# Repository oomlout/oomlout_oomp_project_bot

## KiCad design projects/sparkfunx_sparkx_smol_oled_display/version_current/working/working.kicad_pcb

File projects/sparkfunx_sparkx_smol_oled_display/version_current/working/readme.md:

# OOMP Project  
## SparkX_smol_OLED_Display  by sparkfunX  
  
oomp key: oomp_projects_flat_sparkfunx_sparkx_smol_oled_display  
(snippet of original readme)  
  
- SparkX smôl Header  

[*SparkX smôl OLED Display (SPX-18996)*](https://www.sparkfun.com/products/18996)  
  
The smôl OLED Display is a high contrast, small monochrome display with 128 x 32 pixels. Perfect for applications that don't possess a lot of space but still need to communicate to the user. The display uses the common SSD1306 driver IC fully supported by our blistering fast [SparkFun Qwiic OLED Library](https://github.com/sparkfun/SparkFun_Qwiic_OLED_Arduino_Library).  

-- Repository Contents  
  
- **/Dosuments** - Driver datasheet  
- **/Hardware** - Eagle design files  
- **LICENSE.md** contains the licence information  

-- License Information  
  
This product is _**open source**_!  
  
Please review the LICENSE.md file for license information.  
  
If you have any questions or concerns on licensing, please contact technical support on our [SparkFun forums](https://forum.sparkfun.com/viewforum.php?f=123).  
  
Distributed as-is; no warranty is given.  
  
- Your friends at SparkFun.  
  
  full source readme at [readme_src.md](readme_src.md)  
  
source repo at: [https://github.com/sparkfunX/SparkX_smol_OLED_Display](https://github.com/sparkfunX/SparkX_smol_OLED_Display)  
## Board  

## Schematic  

[schematic pdf](working_schematic.pdf)  
## Images

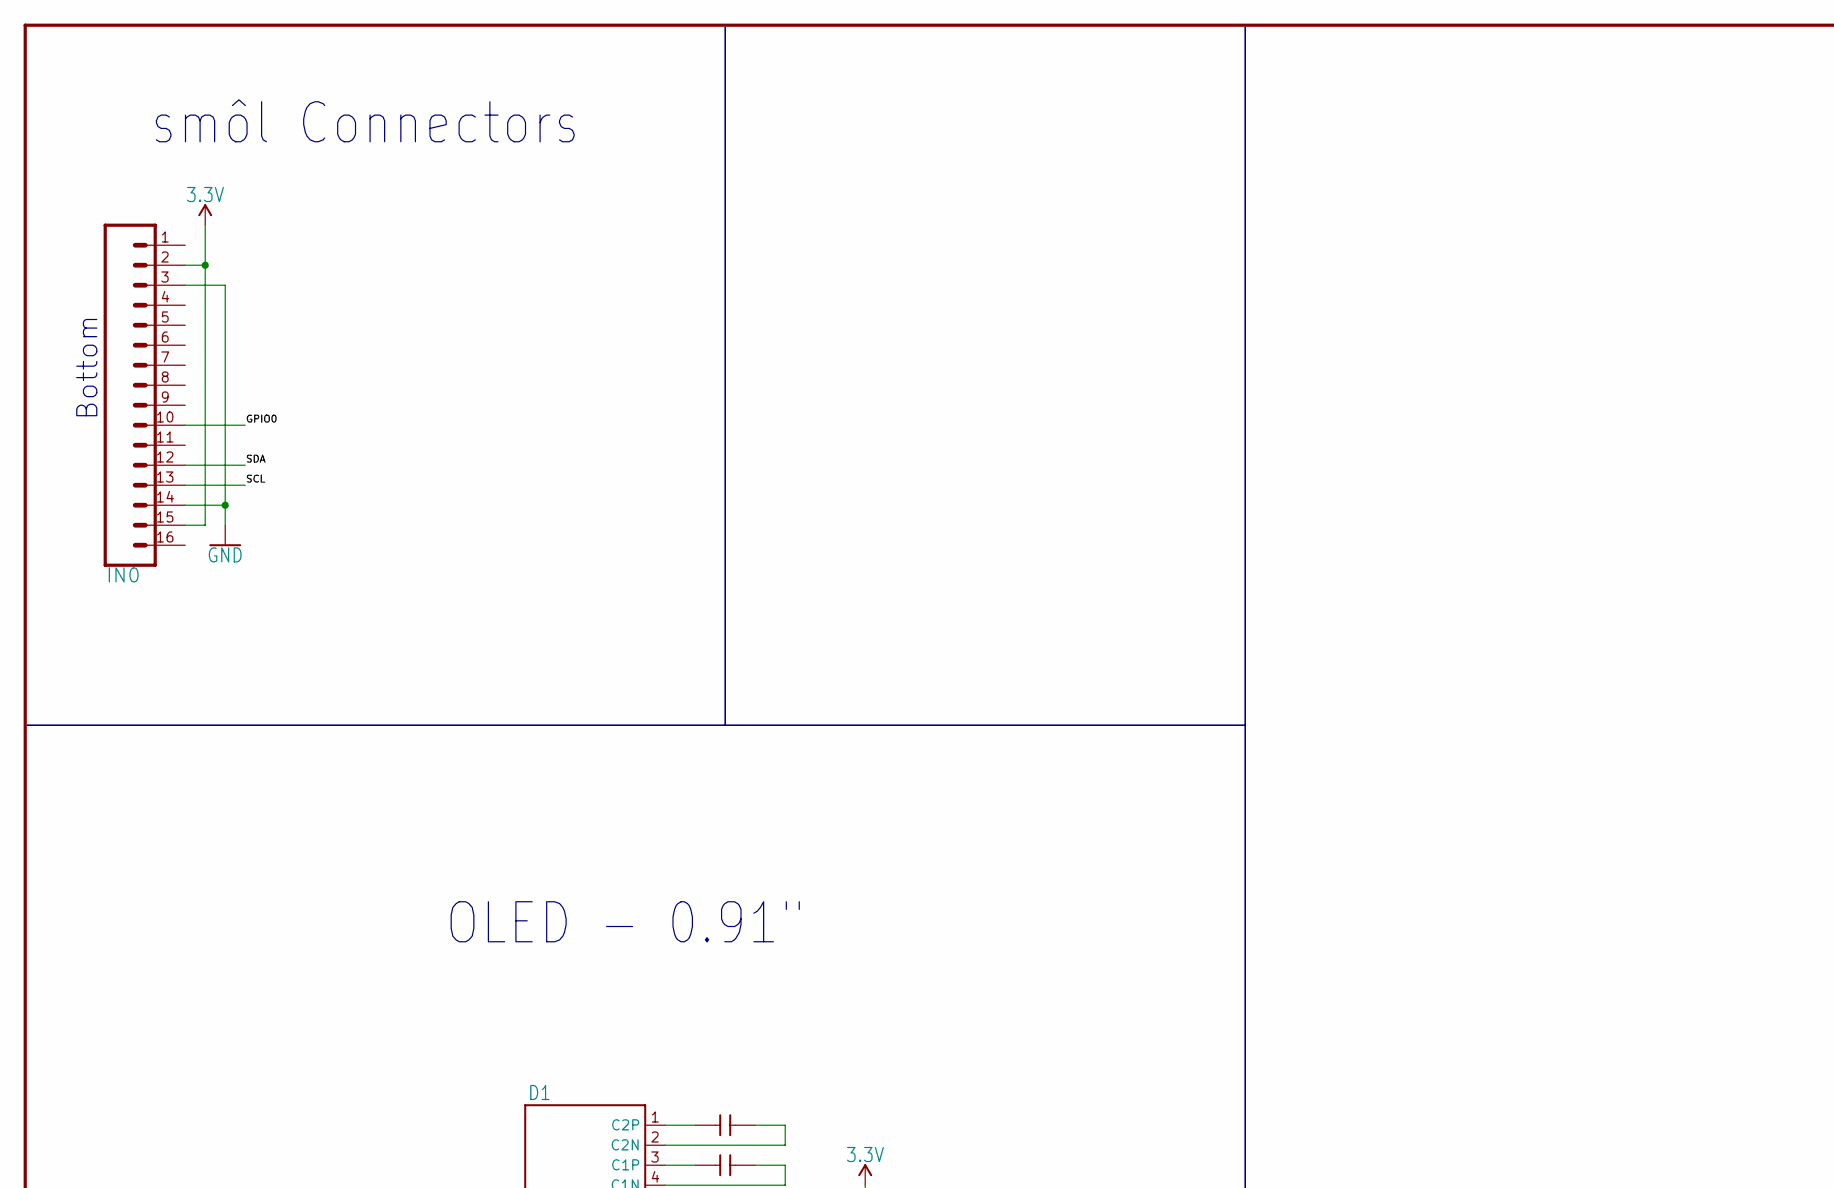
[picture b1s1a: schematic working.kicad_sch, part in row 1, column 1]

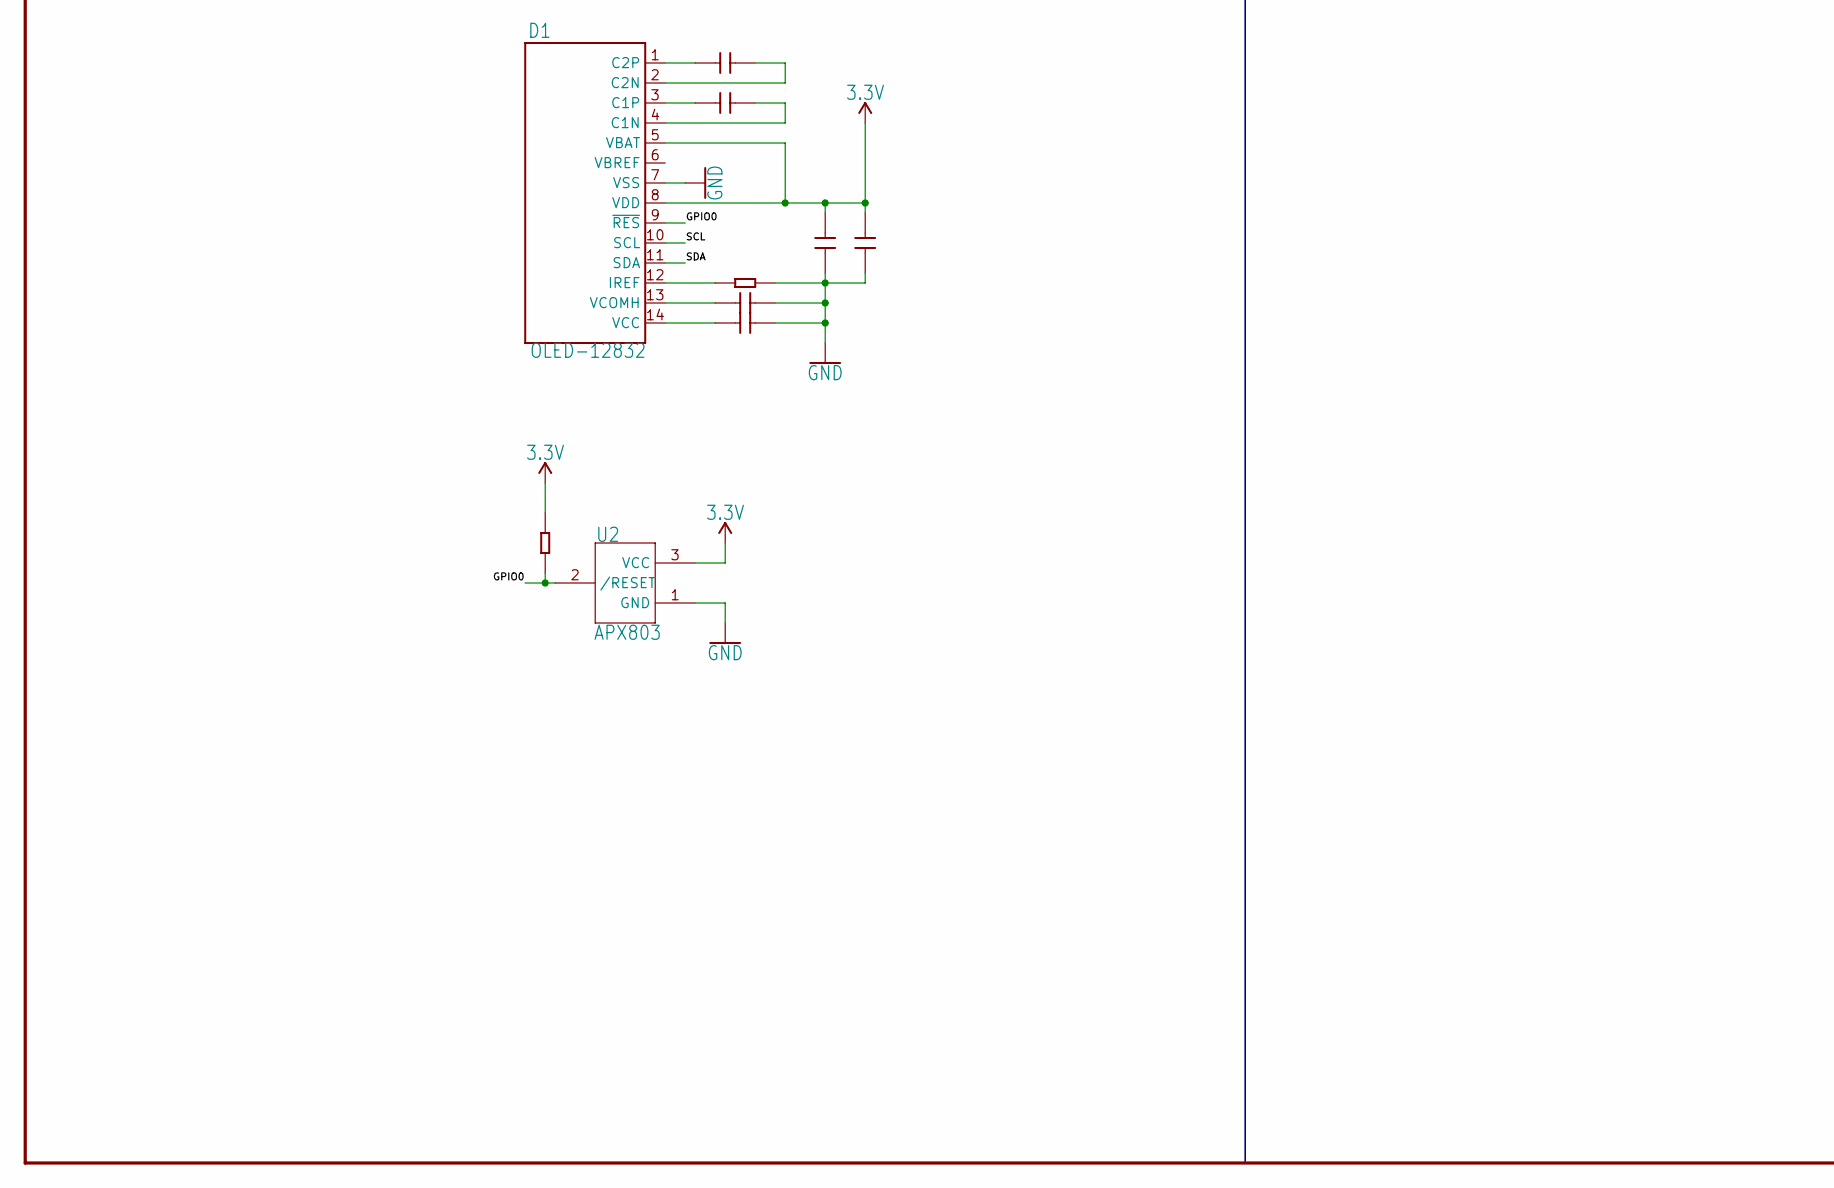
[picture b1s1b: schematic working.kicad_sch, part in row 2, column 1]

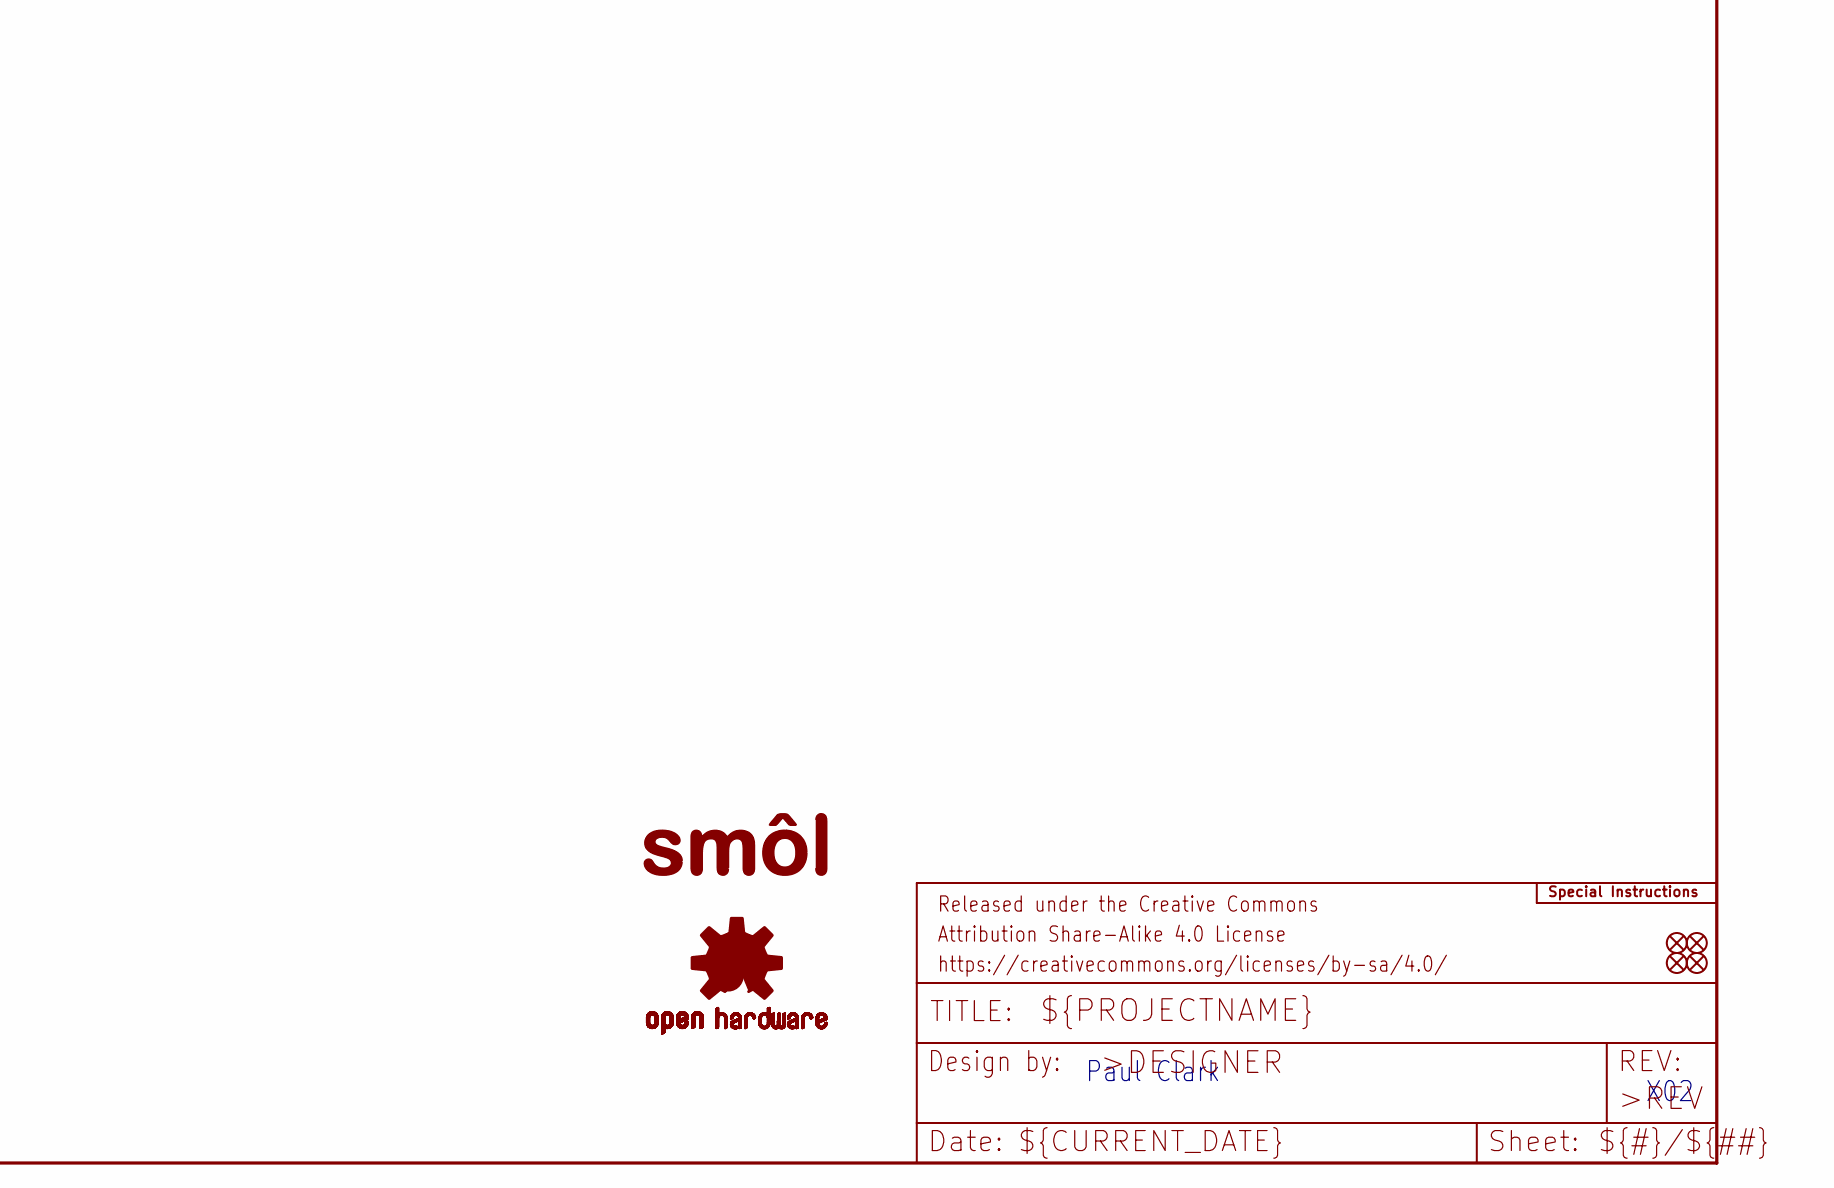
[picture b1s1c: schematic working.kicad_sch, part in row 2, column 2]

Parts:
C1, C2: 1uF ±10% 16V; 0603
C3: 4.7uF ±10% 6.3V; 0603
C4: 0.1uF ±10% 25V; 0603
C5: 2.2uF ±10% 16V; 0603
C6: 4.7uF ±10% 16V; 0603
D1: OLED-12832
FD1, FD2, FD3, FD4: FIDUCIALUFIDUCIAL; FIDUCIAL-MICRO
FRAME1: FRAME-LEDGER; CREATIVE_COMMONS
IN0: CONN_16FPC_16_0.5MM; FPC_16_0.5MM
LOGO1: SPECIAL_INSTRUCTIONS-ORDERING; ORDERING_INSTRUCTIONS
LOGO3: OSHW-LOGOMINI; OSHW-LOGO-MINI
R3: 560K 10%; 0603
R4: 10K ±5%; 0603
U2: APX803; SOT23
U$14: SMOL_LOGOSMALL; SMOL_SMALL

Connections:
3.3V: C3.1, C4.1, D1.5 (VBAT), D1.8 (VDD), IN0.2, IN0.15, R4.2, U2.3 (VCC)
GND: C3.2, C4.2, C5.2, C6.2, D1.7 (VSS), IN0.3, IN0.14, R3.1, U2.1 (GND)
GPIO0: D1.9 (~RES), IN0.10, R4.1, U2.2 (/RESET)
unnamed: C1.2, D1.1 (C2P)
unnamed: C1.1, D1.2 (C2N)
unnamed: C2.2, D1.3 (C1P)
unnamed: C2.1, D1.4 (C1N)
unnamed: C5.1, D1.13 (VCOMH)
unnamed: C6.1, D1.14 (VCC)
unnamed: D1.12 (IREF), R3.2
SCL: D1.10 (SCL), IN0.13
SDA: D1.11 (SDA), IN0.12

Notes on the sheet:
X02
Paul Clark
Bottom
OLED - 0.91"
smôl Connectors

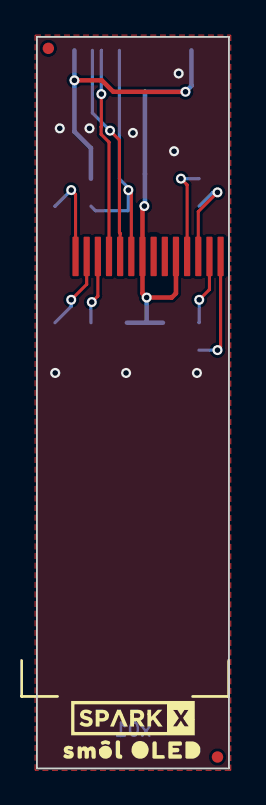
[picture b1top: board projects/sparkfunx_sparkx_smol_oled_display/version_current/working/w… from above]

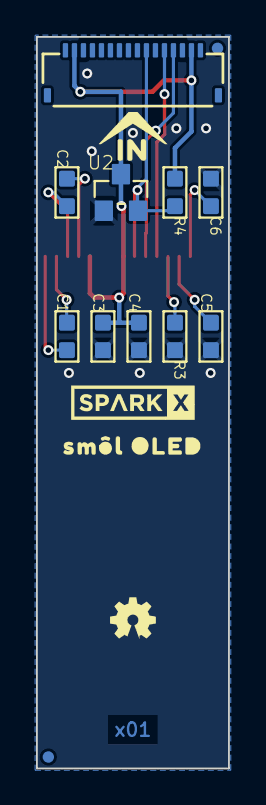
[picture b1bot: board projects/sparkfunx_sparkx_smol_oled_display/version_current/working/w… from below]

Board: 2 copper layers, 10.7 x 40.6 mm, 24 parts (17 on the bottom side), 12 nets.

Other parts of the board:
U$1, U$4: SM�L_OLED0
U$3, U$20: SPARKX-LOGO3; SPARKX-SMALL
U$12: IN0

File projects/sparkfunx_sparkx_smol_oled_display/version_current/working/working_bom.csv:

Row,Description,Part,References,Value,Footprint,Quantity Per PCB,Status,Datasheet
1,,C-0603,C4,0.1uF ±10% 25V,0603,1, ,
2,,C-0603,C1 C2,1uF ±10% 16V,0603,2, ,
3,,C-0603,C5,2.2uF ±10% 16V,0603,1, ,
4,,C-0603,C3 C6,4.7uF ±10% 6.3V,0603,2, ,
5,,OLED-12832,D1,OLED-12832,OLED-12832,1, ,
6,,FRAME-LEDGER,FRAME1,FRAME-LEDGER,CREATIVE_COMMONS,1, ,
7,,CONN_16FPC_16_0.5MM,IN0,CONN_16FPC_16_0.5MM,FPC_16_0.5MM,1, ,
8,,OSHW-LOGOMINI,LOGO3,OSHW-LOGOMINI,OSHW-LOGO-MINI,1, ,
9,,SPECIAL_INSTRUCTIONS-ORDERING,LOGO1,SPECIAL_INSTRUCTIONS-ORDERING,ORDERING_INSTRUCTIONS,1, ,
10,,R-0603,R4,10K ±5%,0603,1, ,
11,,R-0603,R3,560K 10%,0603,1, ,
12,,APX803,U2,APX803,SOT23,1, ,
13,,SMOL_LOGOSMALL,U$14,SMOL_LOGOSMALL,SMOL_SMALL,1, ,





Project info:
Schematic:,working
Variant:,default
Revision:,
Date:,2023-08-06_12-56-17
KiCad Version:,7.0.6-7.0.6~ubuntu22.04.1
Statistics:
Component Groups:,13
Component Count:,15 (0 SMD/ 0 THT)
Fitted Components:,15 (0 SMD/ 0 THT)
Number of PCBs:,1
Total Components:,15

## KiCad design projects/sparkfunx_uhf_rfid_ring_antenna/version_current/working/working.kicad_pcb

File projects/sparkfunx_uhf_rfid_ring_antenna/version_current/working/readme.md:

# UHF_RFID_Ring_Antenna by sparkfunX  
This is a harvested standardized copy of a project from github.  
The original project can be found at:  
https://github.com/sparkfunX/UHF_RFID_Ring_Antenna  
Please consult that link for additional, details, files, and license information.  
Note: It was auto harvested and if the original repo had more than one board file or anything out of the ordinary the files here are likely not representative.

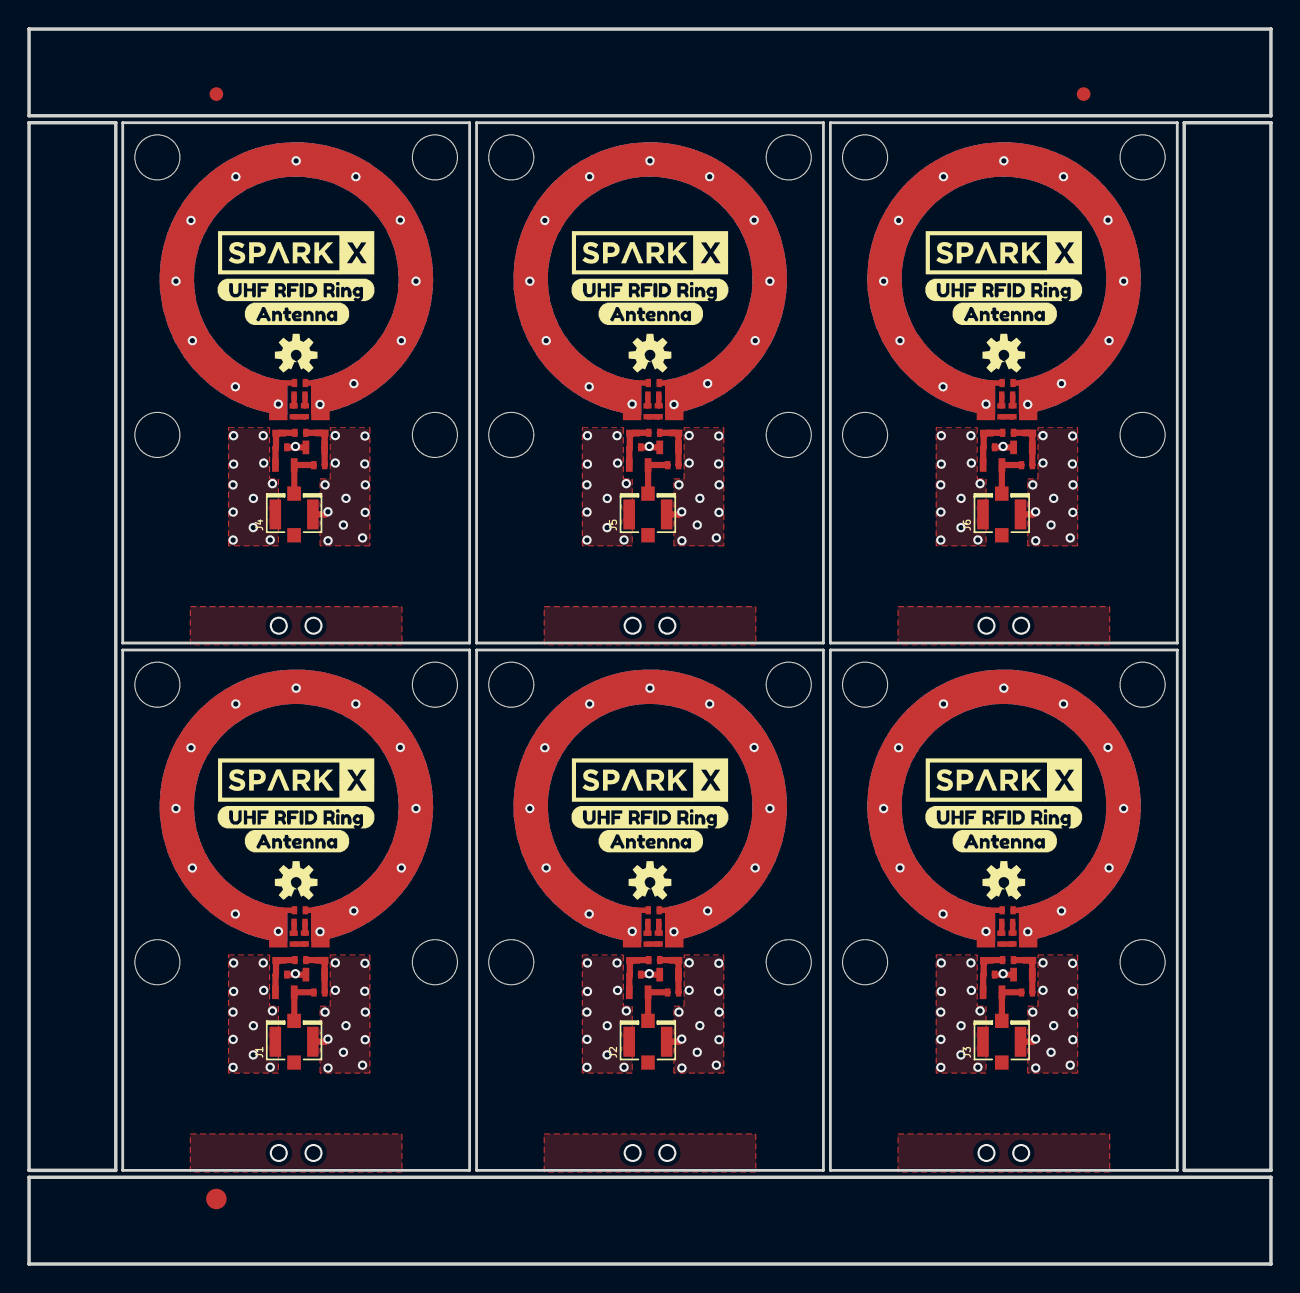
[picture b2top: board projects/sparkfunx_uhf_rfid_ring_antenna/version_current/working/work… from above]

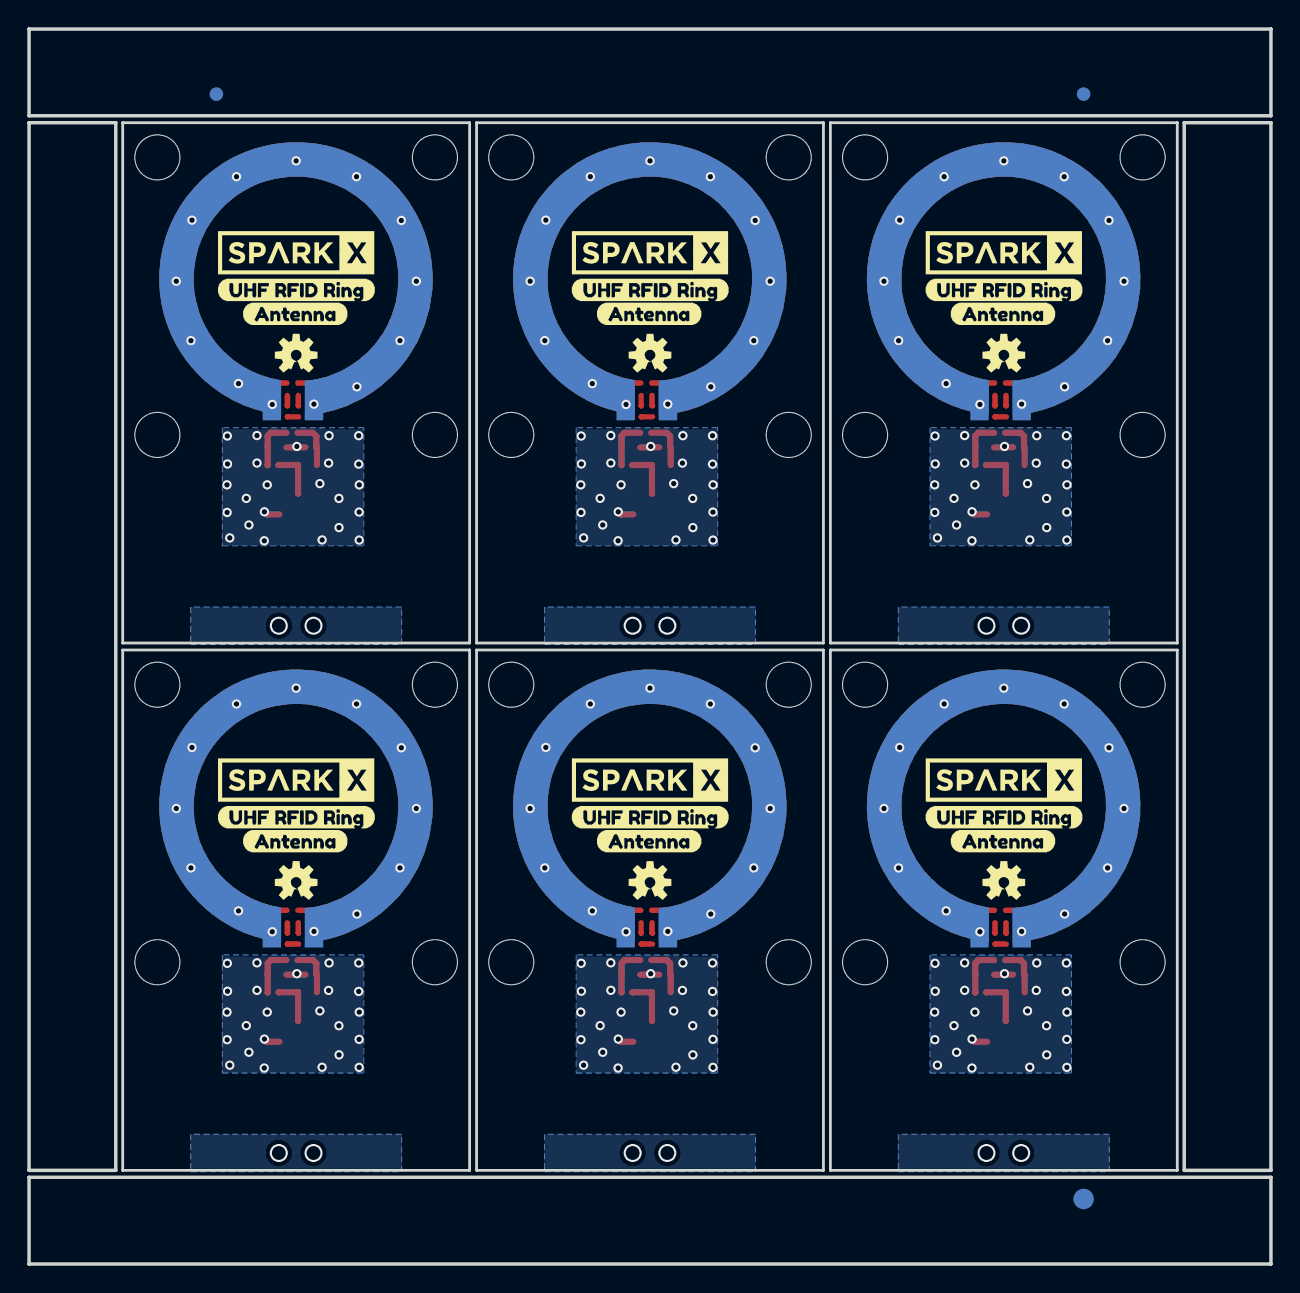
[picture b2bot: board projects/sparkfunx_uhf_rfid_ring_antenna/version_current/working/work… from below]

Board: 2 copper layers, 90.9 x 90.4 mm, 156 parts (33 on the bottom side), 54 nets.

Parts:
C1, C2, C3, C4, C7, C8, C9, C10, C13, C14, C15, C16, C19, C20, C21, C22, C25, C26, C27, C28, C31, C32, C33, C34: 5.0 pF; 0402_MURATA
C5, C6, C11, C12, C17, C18, C23, C24, C29, C30, C35, C36: 2.4 pF; 0402_MURATA
E$1, E$2, E$3, E$4: FIDUCIAL-1X2
E$5, E$6: FIDUCIAL-1.5X3
FRAME1, FRAME2, FRAME3, FRAME4, FRAME5, FRAME6: FRAME-LETTER; CREATIVE_COMMONS
J1, J2, J3, J4, J5, J6: U.FL
L1, L6, L11, L16, L21, L26: 19 nH; 0402_MURATA
L2, L3, L7, L8, L12, L13, L17, L18, L22, L23, L27, L28: 24 nH; 0603_MURATA
L4, L5, L9, L10, L14, L15, L19, L20, L24, L25, L29, L30: 11 nH; 0603_MURATA
R1, R2, R3, R4, R5, R6: 4.28k; 0402_MURATA
U$1, U$2, U$23, U$34, U$45, U$56: ANTENNA; ANT
U$3, U$4, U$13, U$14, U$24, U$25, U$35, U$36, U$46, U$47, U$57, U$58: SPARKX-LARGE
U$5, U$6, U$15, U$16, U$26, U$27, U$37, U$38, U$48, U$49, U$59, U$60: UHF_RFID_RING0
U$7, U$8, U$17, U$18, U$28, U$29, U$39, U$40, U$50, U$51, U$61, U$62: ANTENNA1
U$9, U$10, U$19, U$20, U$30, U$31, U$41, U$42, U$52, U$53, U$63, U$64: OSHW-LOGO-S
U$11, U$21, U$32, U$43, U$54, U$65: QWIIC_BOARD_MOUNT_HOLES
U$12, U$22, U$33, U$44, U$55, U$66: SPARKX-LOGO6; SPARKX-XLARGE

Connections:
A1: C1.P$1, L2.P$2, R1.P$1, U$1.P$1, U$1.P$3
A2: C2.P$2, L3.P$2, R1.P$2, U$1.P$2, U$1.P$4
A3: C7.P$2, C9.P$1
A4: C12.P$1, L6.P$2, L8.P$1, L9.P$1
A5: C14.P$1, C16.P$1
A6: C17.P$2, L11.P$1, L12.P$1, L15.P$2
A7: C21.P$2, C22.P$2
A8: C24.P$2, J4.FEED, L20.P$1
A9: C26.P$2, L23.P$2, R5.P$2, U$45.P$2, U$45.P$4
A10: C29.P$1, J5.1, J5.2, L24.P$2
A11: C36.P$1, L26.P$2, L28.P$1, L29.P$1
C1C1: C8.P$1, C10.P$1
C1C2: C15.P$2, C16.P$2
C1C3: C1.P$2, C3.P$1
C1C4: C20.P$2, L18.P$2, R4.P$2, U$34.P$2, U$34.P$4
C1C5: C30.P$1, L21.P$2, L23.P$1, L24.P$1
C1C6: C35.P$2, L26.P$1, L27.P$1, L30.P$2
C2C1: C9.P$2, C10.P$2
C2C2: C14.P$2, L13.P$2, R3.P$2, U$23.P$2, U$23.P$4
C2C3: C24.P$1, L16.P$2, L18.P$1, L19.P$1
C2C4: C2.P$1, C4.P$1
C2C5: C29.P$2, L21.P$1, L22.P$1, L25.P$2
C2C6: C36.P$2, J6.FEED, L30.P$1
C3C1: C8.P$2, L8.P$2, R2.P$2, U$2.P$2, U$2.P$4
C3C2: C18.P$1, L11.P$2, L13.P$1, L14.P$1
C3C3: C23.P$2, L16.P$1, L17.P$1, L20.P$2
C3C4: C3.P$2, C4.P$2
C3C5: C30.P$2, J5.FEED, L25.P$1
C3C6: C35.P$1, J6.1, J6.2, L29.P$2
GND: C5.P$1, J1.1, J1.2, L4.P$2
L5C1: C11.P$1, J2.1, J2.2, L9.P$2
L5C6: C6.P$2, J1.FEED, L5.P$1
unnamed: C11.P$2, L6.P$1, L7.P$1, L10.P$2
unnamed: C12.P$2, J2.FEED, L10.P$1
unnamed: C6.P$1, L1.P$2, L3.P$1, L4.P$1
unnamed: C5.P$2, L1.P$1, L2.P$1, L5.P$2
unnamed: C13.P$1, L12.P$2, R3.P$1, U$23.P$1, U$23.P$3
unnamed: C13.P$2, C15.P$1
unnamed: C18.P$2, J3.FEED, L15.P$1
unnamed: C17.P$1, J3.1, J3.2, L14.P$2
unnamed: C7.P$1, L7.P$2, R2.P$1, U$2.P$1, U$2.P$3
unnamed: C19.P$1, L17.P$2, R4.P$1, U$34.P$1, U$34.P$3
unnamed: C19.P$2, C21.P$1
unnamed: C20.P$1, C22.P$1
unnamed: C23.P$1, J4.1, J4.2, L19.P$2
unnamed: C25.P$1, L22.P$2, R5.P$1, U$45.P$1, U$45.P$3
unnamed: C25.P$2, C27.P$1
unnamed: C26.P$1, C28.P$1
unnamed: C27.P$2, C28.P$2
unnamed: C31.P$1, L27.P$2, R6.P$1, U$56.P$1, U$56.P$3
unnamed: C31.P$2, C33.P$1
unnamed: C32.P$1, C34.P$1
unnamed: C33.P$2, C34.P$2
unnamed: C32.P$2, L28.P$2, R6.P$2, U$56.P$2, U$56.P$4

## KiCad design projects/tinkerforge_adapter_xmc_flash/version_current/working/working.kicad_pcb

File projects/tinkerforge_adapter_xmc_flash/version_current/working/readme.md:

# OOMP Project  
## adapter-xmc-flash  by Tinkerforge  
  
oomp key: oomp_projects_flat_tinkerforge_adapter_xmc_flash  
(snippet of original readme)  

  full source readme at [readme_src.md](readme_src.md)  
  
source repo at: [https://github.com/Tinkerforge/adapter-xmc-flash](https://github.com/Tinkerforge/adapter-xmc-flash)  
## Board  

## Schematic  

[schematic pdf](working_schematic.pdf)  
## Images

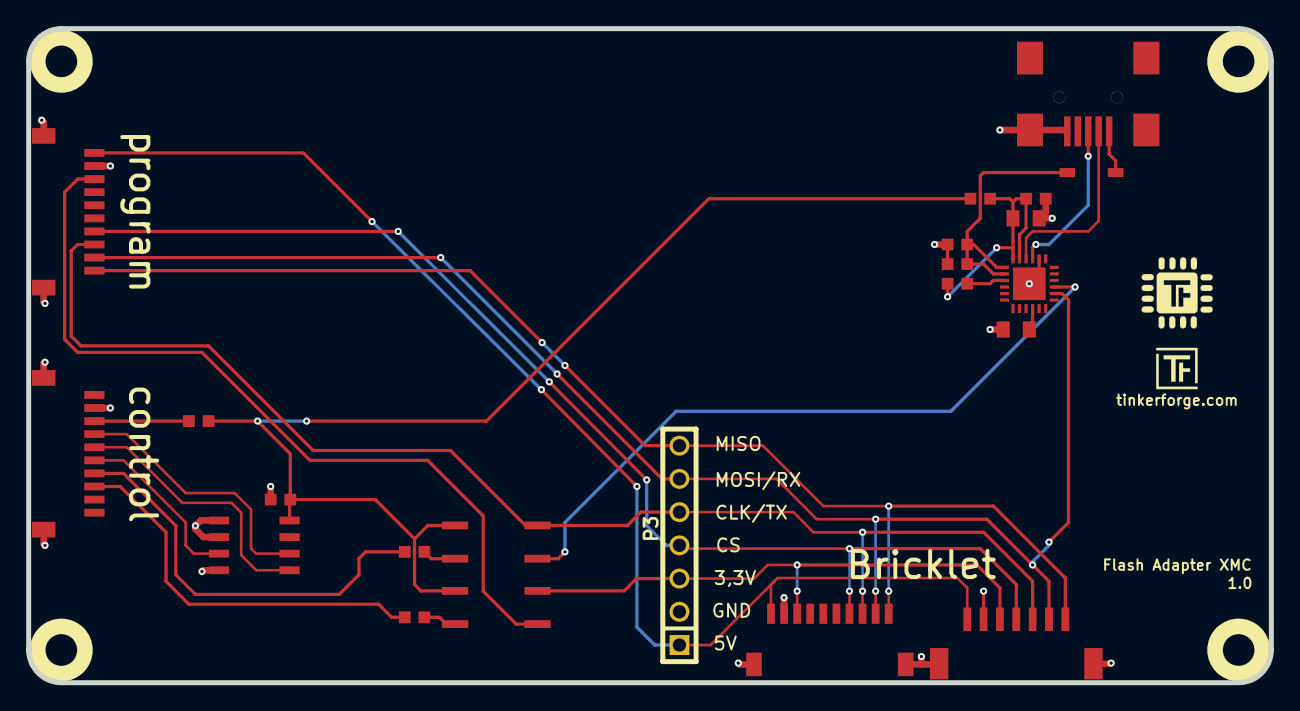
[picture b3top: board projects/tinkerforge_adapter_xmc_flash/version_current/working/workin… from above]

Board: 2 copper layers, 95.0 x 50.0 mm, 26 parts (0 on the bottom side), 25 nets.

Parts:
C1, C2, C5, C6: 100n; C0603F
C3, C4: 4.7µF/10V; C0805
D1: B0520LW; SOD-123
J1: USB-MINI-B-SMD
P1, P4, P5: CON-SENSOR
P2: CON-SENSOR2
P3: CONN_01X07; PIN_ARRAY-7X1
R1: 4k7; R0603F
R2: DNP; R0603F
R3: 0; R0603F
R4, R5: 1k; R0603F
U1: CP2104; QFN-24-4x4-EP
U2: M24C64; SOIC8
U3, U4: CPC1020N; SOP4-WIDE
U5, U6, U7, U8: DRILL; DRILL_NP

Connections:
3V3: C6.1, R2.1, R3.1, U2.8, U3.1, U4.1
GND: C1.2, C2.2, C3.2, C4.2, C5.2, C6.2, J1.5, J1.6, P1.2, P1.EP, P2.2, P2.EP, P3.2, P4.2, P4.EP, P5.2, P5.EP, U1.2, U1.25, U2.1, U2.2, U2.4
unnamed: C1.1, C2.1, D1.2, U1.7, U1.8
unnamed: C3.1, U1.16
unnamed: C4.1, C5.1, R1.1, R2.2, U1.5, U1.6
unnamed: D1.1, J1.1
unnamed: J1.2, U1.4
unnamed: J1.3, U1.3
unnamed: P1.1, P2.1, P3.1, P4.1
unnamed: P1.7, P2.4, P3.4, P4.7
unnamed: P1.10, P2.7, P3.7, P4.10
unnamed: P5.3, R3.2
unnamed: P5.4, U2.6
unnamed: P5.5, U2.5
unnamed: P5.6, U2.3
unnamed: P5.7, R4.2
unnamed: P5.8, R5.2
unnamed: R1.2, U1.9
unnamed: R4.1, U4.2
unnamed: R5.1, U3.2
POWER_RIN: P4.3, U3.3
POWER_ROUT: P1.3, P2.3, P3.3, U3.4
RXD: P1.9, P2.6, P3.6, P4.9, U1.20
TX_RIN: U1.21, U4.3
TX_ROUT: P1.8, P2.5, P3.5, P4.8, U4.4

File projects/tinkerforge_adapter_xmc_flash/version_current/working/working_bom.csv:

"Id";"Designator";"Footprint";"Quantity";"Designation";"Supplier and ref";
1;"U4,U3";"SOP4-WIDE";2;"CPC1020N";;;
2;"G***";"Logo_CoMCU";1;"LOGO";;;
3;"U8,U7,U6,U5";"DRILL_NP";4;"DRILL";;;
4;"U2";"SOIC8";1;"M24C64";;;
5;"U1";"QFN-24-4x4-EP";1;"CP2104";;;
6;"P5,P4,P1";"CON-SENSOR";3;"CON-SENSOR";;;
7;"P3";"PIN_ARRAY-7X1";1;"CONN_01X07";;;
8;"P2";"CON-SENSOR2";1;"CON-SENSOR2";;;
9;"J1";"USB-MINI-B-SMD";1;"USB-MINI-B-SMD";;;
10;"D1";"SOD-123";1;"B0520LW";;;
11;"G***";"Logo_31x31";1;"Logo_31x31";;;
12;"C1,C2,C5,C6";"C0603F";4;"100n";;;
13;"C3,C4";"C0805";2;"4.7µF/10V";;;
14;"R1";"R0603F";1;"4k7";;;
15;"R2";"R0603F";1;"DNP";;;
16;"R3";"R0603F";1;"0";;;
17;"R4,R5";"R0603F";2;"1k";;;

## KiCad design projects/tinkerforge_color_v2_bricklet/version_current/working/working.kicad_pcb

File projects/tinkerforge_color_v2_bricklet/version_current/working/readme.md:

# color-v2-bricklet by Tinkerforge  
This is a harvested standardized copy of a project from github.  
The original project can be found at:  
https://github.com/Tinkerforge/color-v2-bricklet  
Please consult that link for additional, details, files, and license information.  
Note: It was auto harvested and if the original repo had more than one board file or anything out of the ordinary the files here are likely not representative.

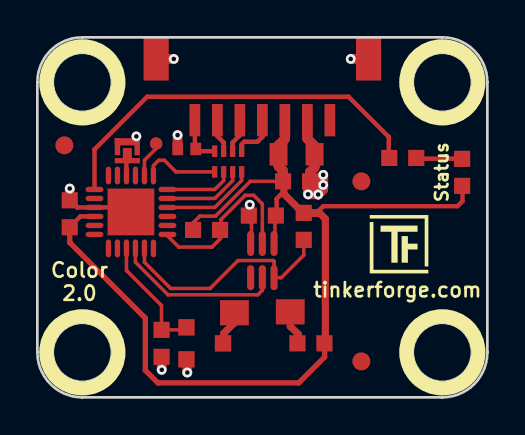
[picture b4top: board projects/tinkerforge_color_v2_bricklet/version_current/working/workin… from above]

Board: 2 copper layers, 25.0 x 20.0 mm, 28 parts (2 on the bottom side), 20 nets.

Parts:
C1, C5: 100nF; C0603F
C2: 220pF; C0402F
C3: 10uF; C0805
C4: 1uF; C0603F
D1: LED; LED-3x2
D2: blue; D0603F
Fiducial_Mark: VAL**; Fiducial_Mark
Fiducial_Mark#2, Fiducial_Mark#3: VAL**; Fiducial_Mark
P1: CON-SENSOR2
P2: DEBUG; DEBUG_PAD
P3: BOOT; SolderJumper
Q1: 2N7002P; SOT23GDS
R1: 10k; R0603F
R2: 180; R0603F
R3, R4: 2k2; R0603F
R5: 1k; R0603F
RP1: 82; 4X0402
U1: TCS3472; FN-TCS3472
U2: XMC1300; QFN24-4x4mm-0.5mm
U3, U4, U5, U6: DRILL; DRILL_NP
VAL: CE_5mm
VAL#2: WEEE_7mm

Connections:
GND: C1.1, C2.2, C3.2, C4.2, C5.2, P1.2, P1.EP, P3.1, Q1.S, R1.2, U1.3, U2.9, U2.EXP
INT: U1.5, U2.16
LED: Q1.G, R1.1, U2.15
unnamed: C2.1, P1.7, RP1.4
unnamed: D1.1, R2.2
unnamed: D1.2, Q1.D
unnamed: D2.2, R5.2
unnamed: P1.4, RP1.1
unnamed: P1.5, RP1.2
unnamed: P1.6, RP1.3
unnamed: P2.1, U2.2
unnamed: P3.2, U2.4
unnamed: R5.1, U2.7
S-CLK: RP1.7, U2.23
S-CS: RP1.8, U2.22
S-MISO: RP1.5, U2.1
S-MOSI: RP1.6, U2.24
SCL: R3.2, U1.2, U2.19
SDA: R4.2, U1.6, U2.17
VCC: C1.2, C3.1, C4.1, C5.1, D2.1, P1.3, R2.1, R3.1, R4.1, U1.1, U2.10

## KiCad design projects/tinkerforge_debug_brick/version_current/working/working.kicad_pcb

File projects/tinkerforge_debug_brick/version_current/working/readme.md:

# OOMP Project  
## debug-brick  by Tinkerforge  
  
oomp key: oomp_projects_flat_tinkerforge_debug_brick  
(snippet of original readme)  

  full source readme at [readme_src.md](readme_src.md)  
  
source repo at: [https://github.com/Tinkerforge/debug-brick](https://github.com/Tinkerforge/debug-brick)  
## Board  

## Schematic  

[schematic pdf](working_schematic.pdf)  
## Images

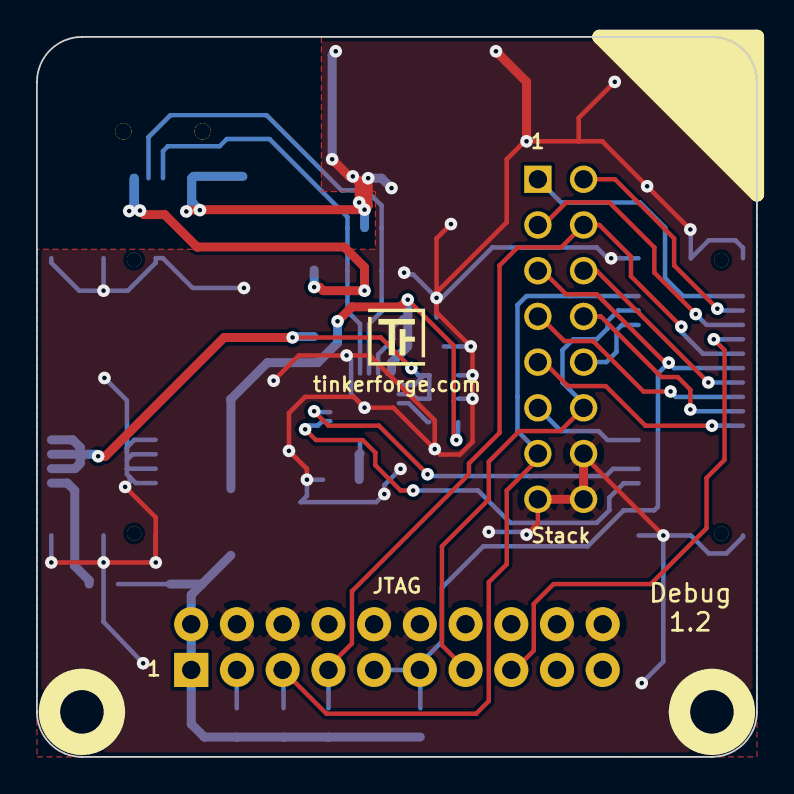
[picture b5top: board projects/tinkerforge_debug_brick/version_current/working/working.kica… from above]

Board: 2 copper layers, 40.0 x 40.0 mm, 25 parts (0 on the bottom side), 27 nets.

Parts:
C1, C2, C5: 100nF; C0603
C3, C4: 4.7µF/10V; C0805
D1, D2: B0520LW; SOD-123
J1, J3: STACK-DOWN; BTB08-ACS-BTM
J2: USB-MINI-B-SMD
P1: CONN_16; pin_array_8x2
P2: JTAG; pin_array_10x2
R1, R2, R3, R4: 100k; R0603
R5: 4k7; R0603
R6: 0; R0603
U1: CM1293A; SC-74
U2: CP2104; QFN-24-4x4-EP
U3, U4, U5: DRILL; DRILL_NP
VAL: CE_5mm
VAL#2: WEEE_7mm

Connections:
+3V3: D2.2, P2.1, P2.2, R1.1, R2.1, R3.1, R4.1, R6.2
+5V: C1.1, C2.1, D1.2, J3.22, J3.24, J3.26, U2.7, U2.8
EX-SEL: J1.22, P1.11
GND: C1.2, C2.2, C3.2, C4.2, C5.2, J1.EP, J2.5, J2.6, J3.21, J3.23, J3.25, J3.27, J3.EP, P1.14, P1.15, P1.16, P2.4, P2.6, P2.8, P2.10, P2.12, P2.14, P2.16, P2.18, P2.20, U1.2, U2.2, U2.25
unnamed: C3.1, U2.16
unnamed: C4.1, C5.1, D2.1, R5.2, U2.5, U2.6
unnamed: D1.1, J2.1, U1.5
unnamed: J1.1, P1.1
unnamed: J1.3, P1.2
unnamed: J1.5, P1.3
unnamed: J1.7, P2.15
unnamed: J1.9, P1.4, P2.7, R2.2
unnamed: J1.11, P1.5, P2.9, P2.11, R3.2
unnamed: J1.13, P1.6
unnamed: J1.15, P1.7
unnamed: J1.17, P1.8
unnamed: J1.19, P1.9
unnamed: J2.2, U1.3, U1.4, U2.4
unnamed: J2.3, U1.1, U1.6, U2.3
unnamed: J3.28, R6.1
unnamed: P2.3, R4.2
unnamed: R5.1, U2.9
RXD: J1.26, U2.21
SCL: J1.4, P1.12, P2.13
SDA: J1.2, P1.13, P2.5, R1.2
SEL: J1.6, P1.10
TXD: J1.28, U2.20

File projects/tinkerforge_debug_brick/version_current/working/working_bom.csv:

"Id";"Designator";"Footprint";"Quantity";"Designation";"Supplier and ref";
1;"VAL";"CE_5mm";1;"CE_5mm";;;
2;"VAL";"WEEE_7mm";1;"WEEE_7mm";;;
3;"G***";"Logo_31x31";1;"Logo_31x31";;;
4;"D1,D2";"SOD-123";2;"B0520LW";;;
5;"R1,R2,R3,R4";"R0603";4;"100k";;;
6;"U1";"SC-74";1;"CM1293A";;;
7;"U3,U4,U5";"DRILL_NP";3;"DRILL";;;
8;"P2";"pin_array_10x2";1;"JTAG";;;
9;"P1";"pin_array_8x2";1;"CONN_16";;;
10;"C1,C2,C5";"C0603";3;"100nF";;;
11;"C3,C4";"C0805";2;"4.7µF/10V";;;
12;"R5";"R0603";1;"4k7";;;
13;"R6";"R0603";1;"0";;;
14;"U2";"QFN-24-4x4-EP";1;"CP2104";;;
15;"J3,J1";"BTB08-ACS-BTM";2;"STACK-DOWN";;;
16;"J2";"USB-MINI-B-SMD";1;"USB-MINI-B-SMD";;;

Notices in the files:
projects/sparkfunx_sparkx_smol_oled_display/version_current/working/working.kicad_sch:
https://creativecommons.org/licenses/by-sa/4.0
Released under the Creative Commons
projects/tinkerforge_adapter_xmc_flash/version_current/working/working.kicad_pcb:
Licensed under CERN OHL v.1.1
Copyright (©) 2017, L.Lauer
Copyright Tinkerforge GmbH 2015.
This documentation describes Open Hardware and is licensed under the
CERN OHL v. 1.1.
projects/tinkerforge_adapter_xmc_flash/version_current/working/working.kicad_sch:
Copyright Tinkerforge GmbH 2017.
